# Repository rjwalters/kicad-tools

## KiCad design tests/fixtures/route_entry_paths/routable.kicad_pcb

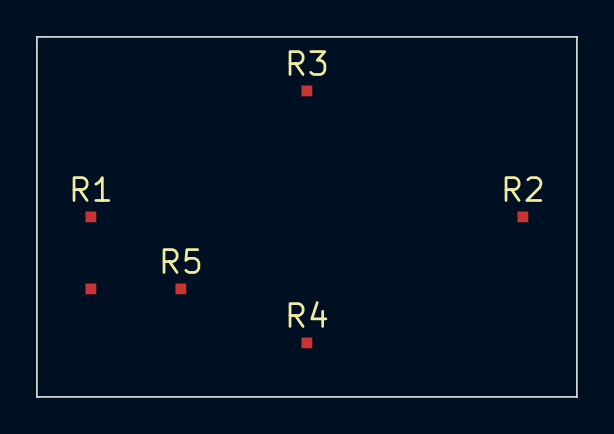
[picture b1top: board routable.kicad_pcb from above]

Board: 2 copper layers, 30.0 x 20.0 mm, 5 parts (0 on the bottom side), 3 nets, no tracks yet.

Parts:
R1, R2, R3, R4, R5: 10k; R_0603_1608Metric

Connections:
/A: R1.1, R2.1
/B: R3.1, R4.1
/C: R1.2, R5.1

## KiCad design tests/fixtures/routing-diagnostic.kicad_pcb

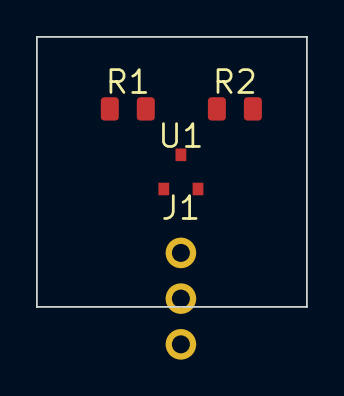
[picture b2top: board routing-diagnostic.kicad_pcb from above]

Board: 2 copper layers, 15.0 x 15.0 mm, 4 parts (0 on the bottom side), 4 nets, no tracks yet.

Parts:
J1: Conn_01x03; PinHeader_1x03_P2.54mm_Vertical
R1, R2: 10k; R_0805_2012Metric
U1: SOT-23-3

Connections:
NET1: J1.1, R1.1, U1.1
NET2: R1.2, R2.1
NET3: J1.2, R2.2, U1.2
NET4: J1.3, U1.3

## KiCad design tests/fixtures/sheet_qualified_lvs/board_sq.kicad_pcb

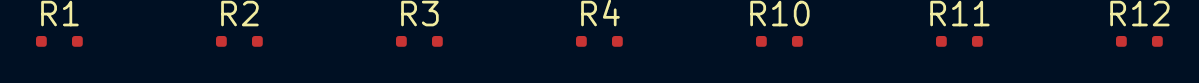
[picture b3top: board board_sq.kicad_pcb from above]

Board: 2 copper layers, 7 parts (0 on the bottom side), 6 nets, no tracks yet.

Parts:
R1: 1k; R_0402_1005Metric
R2: 2k; R_0402_1005Metric
R3: 3k; R_0402_1005Metric
R4: 4k; R_0402_1005Metric
R10: 10k; R_0402_1005Metric
R11: 22k; R_0402_1005Metric
R12: 33k; R_0402_1005Metric

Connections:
/AUX/DBG_LED: R3.2, R4.2
/BUS: R1.1, R10.1
/MCU/DBG_LED: R1.2, R2.2
/SENSE: R11.1, R12.1
GLOBAL_NET: R2.1, R11.2
GND: R3.1, R4.1, R10.2, R12.2

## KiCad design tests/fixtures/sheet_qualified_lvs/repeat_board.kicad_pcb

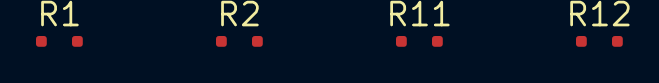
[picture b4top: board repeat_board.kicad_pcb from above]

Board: 2 copper layers, 4 parts (0 on the bottom side), 3 nets, no tracks yet.

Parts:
R1, R11: 1k; R_0402_1005Metric
R2, R12: 2k; R_0402_1005Metric

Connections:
/MCU_A/DBG_LED: R1.2, R2.2
/MCU_B/DBG_LED: R11.2, R12.2
GND: R1.1, R2.1, R11.1, R12.1
